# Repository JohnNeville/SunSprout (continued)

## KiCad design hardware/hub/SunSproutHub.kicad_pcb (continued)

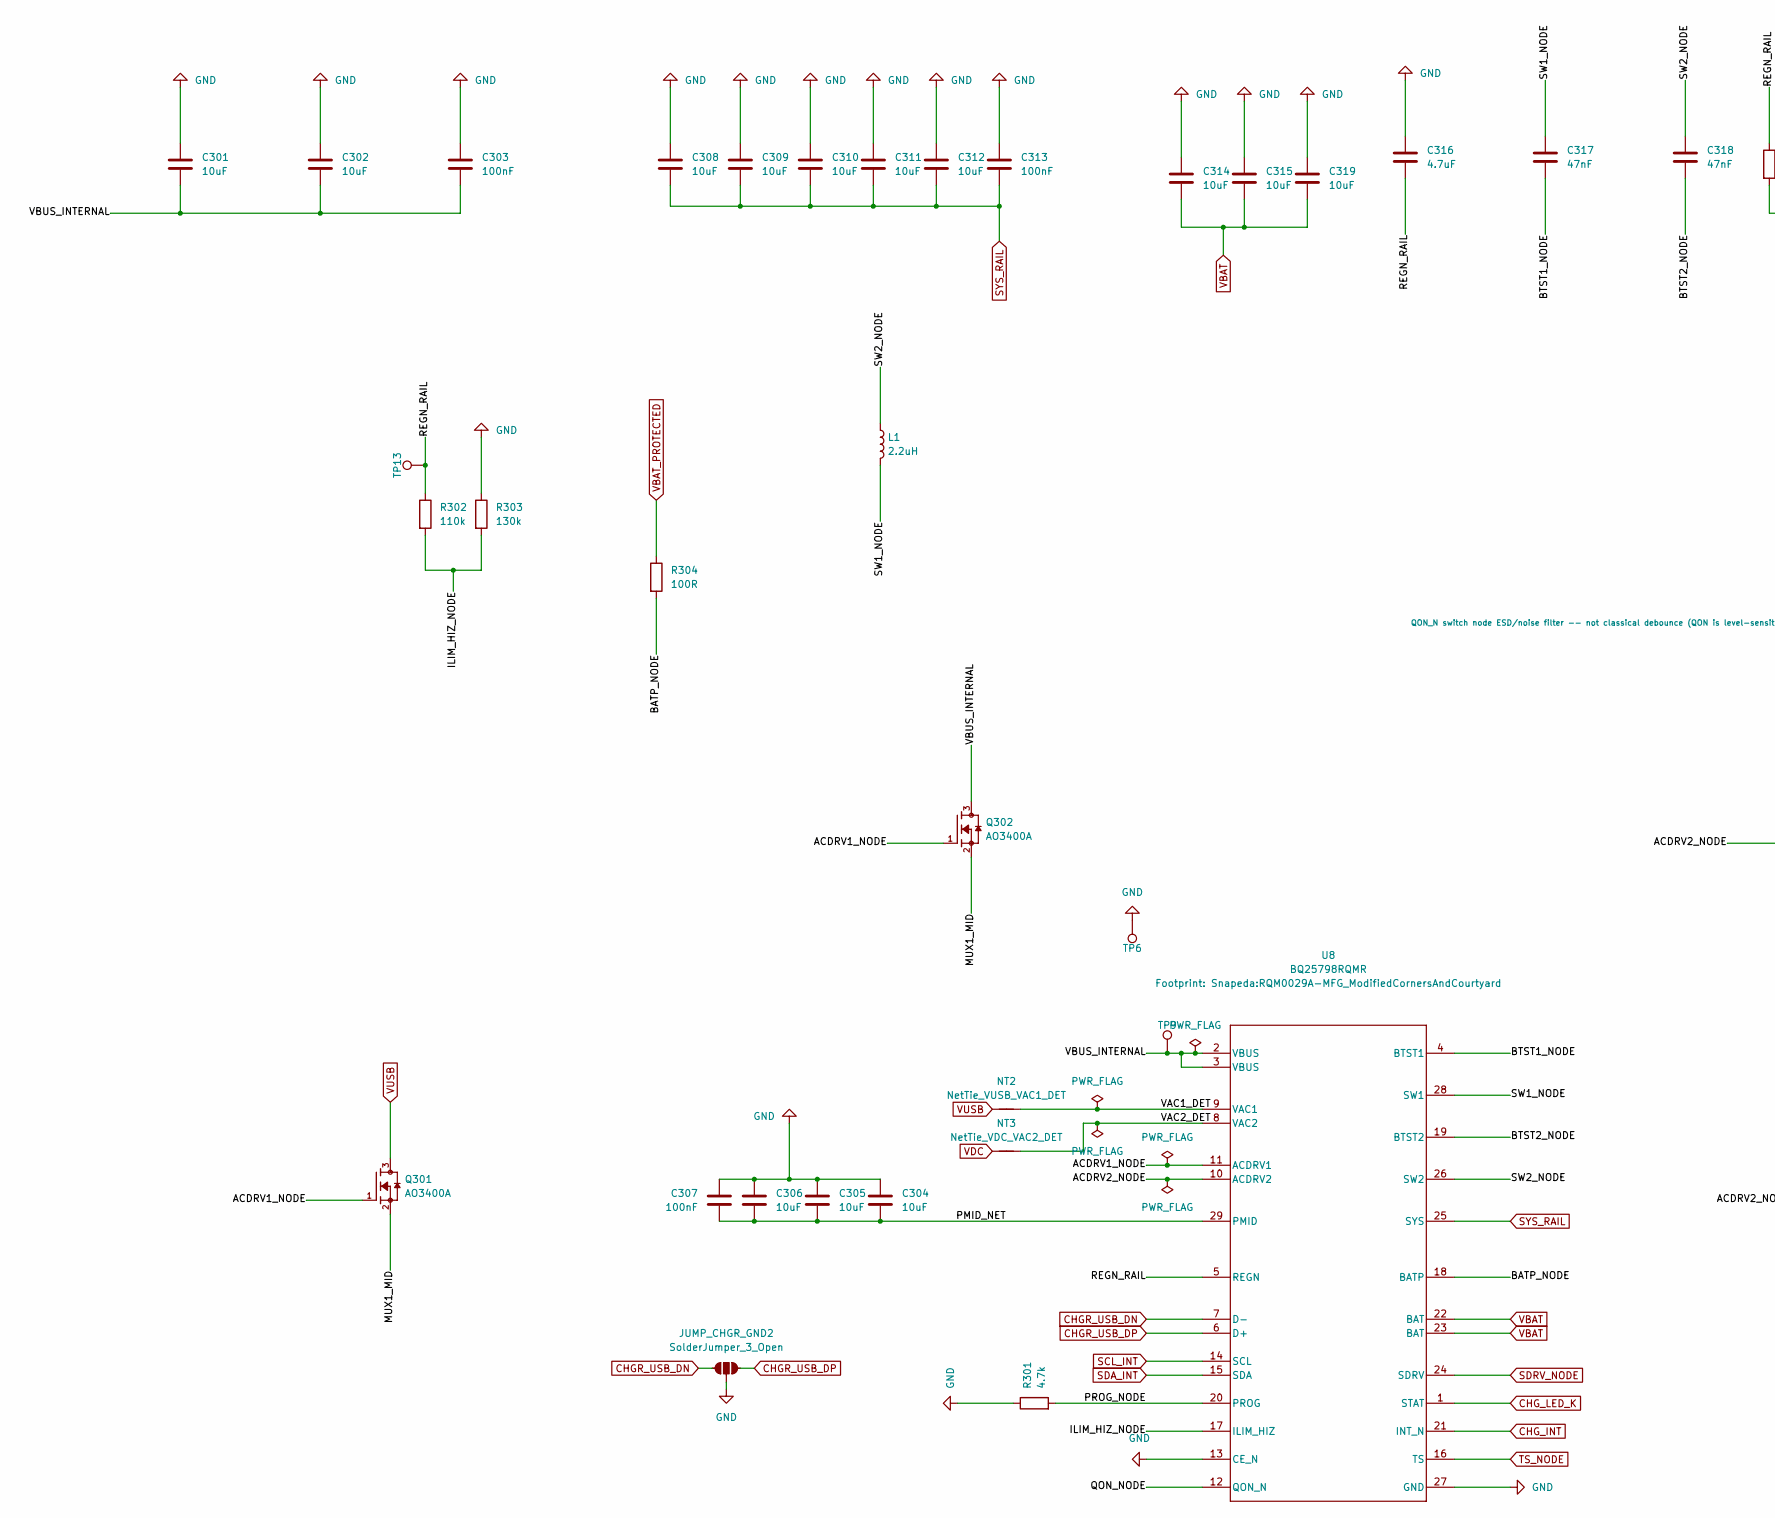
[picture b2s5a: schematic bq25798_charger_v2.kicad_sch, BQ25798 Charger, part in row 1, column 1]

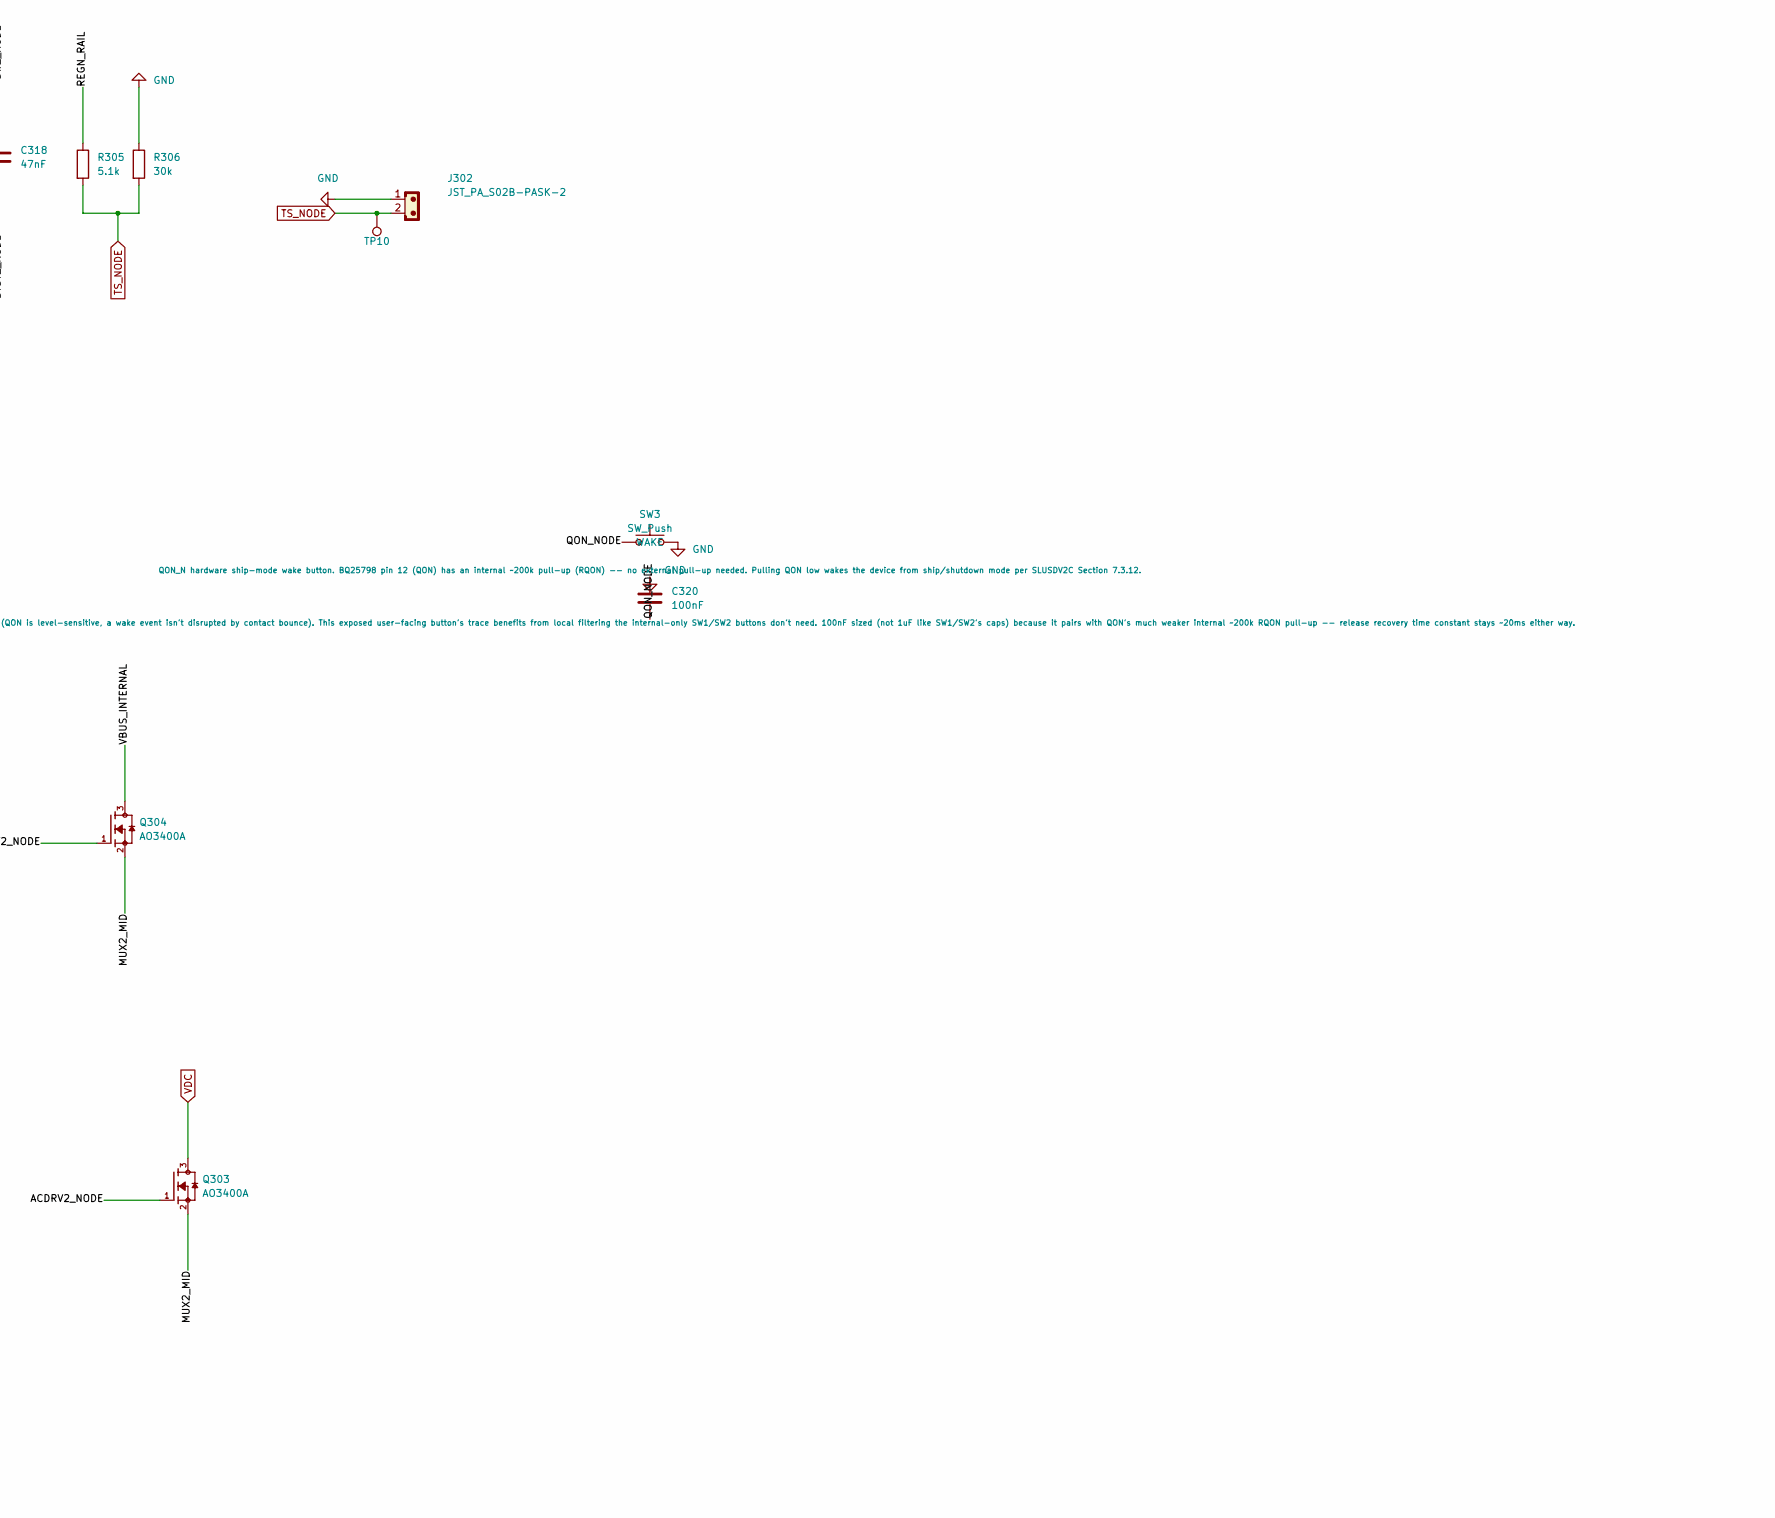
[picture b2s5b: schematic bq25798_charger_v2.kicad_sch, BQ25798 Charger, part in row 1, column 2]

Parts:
C301, C302, C304, C305, C306: 10uF; C_0805_2012Metric; MPN GRM21BR61H106KE43L; LCSC Part C440198
C303, C307, C313, C320: 100nF; C_0402; MPN CL05B104KB54PNC; LCSC Part C307331
C308, C309, C310, C311, C312, C314, C315, C319: 10uF; C_0603_1608Metric; MPN CL10A106MA8NRNC; LCSC Part C96446
C316: 4.7uF; C_0805_2012Metric; MPN CL21A475KAQNNNE; LCSC Part C1779
C317, C318: 47nF; C_0603_1608Metric; MPN CL10B473KB8NNNC; LCSC Part C1622
J302: JST_PA_S02B-PASK-2; JST_PA_S02B-PASK-2_1x02_P2.00mm_Horizontal; MPN S02B-PASK-2(LF)(SN); LCSC Part C265094
JUMP_CHGR_GND2: SolderJumper_3_Open; SolderJumper-3_P1.3mm_Open_RoundedPad1.0x1.5mm_NumberLabels
L1: 2.2uH; L_Changjiang_FTC404030S; MPN FTC404030S2R2MGCA; LCSC Part C39676081
NT2: NetTie_VUSB_VAC1_DET; NetTie-2_SMD_Pad0.5mm
NT3: NetTie_VDC_VAC2_DET; NetTie-2_SMD_Pad0.5mm
Q301, Q302, Q303, Q304: AO3400A; SOT95P280X125-3N; MPN AO3400A; LCSC Part C20917
R301: 4.7k; R_0603_1608Metric; MPN 0603WAF4701T5E; LCSC Part C23162
R302: 110k; R_0603_1608Metric; MPN 0603WAF1103T5E; LCSC Part C25805
R303: 130k; R_0603_1608Metric; MPN 0603WAF1303T5E; LCSC Part C22795
R304: 100R; R_0603_1608Metric; MPN 0603WAF1000T5E; LCSC Part C22775
R305: 5.1k; R_0603_1608Metric; MPN 0603WAF5101T5E; LCSC Part C23186
R306: 30k; R_0603_1608Metric; MPN 0603WAF3002T5E; LCSC Part C22984
SW3: SW_Push; SW_SPST_TS-1088-xR020; MPN TS-1088-AR02016; LCSC Part C720477
TP6: GND; TestPoint-1.0mm
TP9: VBUS_INTERNAL; TestPoint-1.0mm
TP10: TS_NODE; TestPoint-1.0mm
TP13: REGN_RAIL; TestPoint-1.0mm
U8: BQ25798RQMR; RQM0029A-MFG_ModifiedCornersAndCourtyard; MPN BQ25798RQMR; LCSC Part C2876593

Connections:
/BQ25798 Charger/ACDRV1_NODE: Q301.1, Q302.1, U8.11 (ACDRV1)
/BQ25798 Charger/ACDRV2_NODE: Q303.1, Q304.1, U8.10 (ACDRV2)
/BQ25798 Charger/BATP_NODE: R304.2, U8.18 (BATP)
/BQ25798 Charger/BTST1_NODE: C317.2, U8.4 (BTST1)
/BQ25798 Charger/BTST2_NODE: C318.2, U8.19 (BTST2)
/BQ25798 Charger/ILIM_HIZ_NODE: R302.2, R303.2, U8.17 (ILIM_HIZ)
/BQ25798 Charger/MUX1_MID: Q301.2, Q302.2
/BQ25798 Charger/MUX2_MID: Q303.2, Q304.2
/BQ25798 Charger/PMID_NET: C304.2, C305.2, C306.2, C307.2, U8.29 (PMID)
/BQ25798 Charger/PROG_NODE: R301.2, U8.20 (PROG)
/BQ25798 Charger/QON_NODE: C320.2, SW3.1, U8.12 (QON_N)
/BQ25798 Charger/REGN_RAIL: C316.2, R302.1, R305.1, TP13.1 (1_1), U8.5 (REGN)
/BQ25798 Charger/SW1_NODE: C317.1, L1.2, U8.28 (SW1)
/BQ25798 Charger/SW2_NODE: C318.1, L1.1, U8.26 (SW2)
/BQ25798 Charger/VAC1_DET: NT2.2, U8.9 (VAC1)
/BQ25798 Charger/VAC2_DET: NT3.2, U8.8 (VAC2)
/BQ25798 Charger/VBUS_INTERNAL: C301.2, C302.2, C303.2, Q302.3, Q304.3, TP9.1 (1_1), U8.2 (VBUS), U8.3 (VBUS)
CHGR_USB_DN: JUMP_CHGR_GND2.1 (A), U8.7 (D-); also elsewhere on the board
CHGR_USB_DP: JUMP_CHGR_GND2.3 (C), U8.6 (D+); also elsewhere on the board
CHG_INT: U8.21 (INT_N); also elsewhere on the board
CHG_LED_K: U8.1 (STAT); also elsewhere on the board
GND: C301.1, C302.1, C303.1, C304.1, C305.1, C306.1, C307.1, C308.1, C309.1, C310.1, C311.1, C312.1, C313.1, C314.1, C315.1, C316.1, C319.1, C320.1, J302.1, JUMP_CHGR_GND2.2 (B), R301.1, R303.1, R306.1, SW3.2, TP6.1 (1_1), U8.13 (CE_N), U8.27 (GND); also elsewhere on the board
SCL_INT: U8.14 (SCL); also elsewhere on the board
SDA_INT: U8.15 (SDA); also elsewhere on the board
SDRV_NODE: U8.24 (SDRV); also elsewhere on the board
SYS_RAIL: C308.2, C309.2, C310.2, C311.2, C312.2, C313.2, U8.25 (SYS); also elsewhere on the board
TS_NODE: J302.2, R305.2, R306.2, TP10.1 (1_1), U8.16 (TS)
VBAT: C314.2, C315.2, C319.2, U8.22 (BAT), U8.23 (BAT); also elsewhere on the board
VBAT_PROTECTED: R304.1; also elsewhere on the board
VDC: NT3.1, Q303.3; also elsewhere on the board
VUSB: NT2.1, Q301.3; also elsewhere on the board

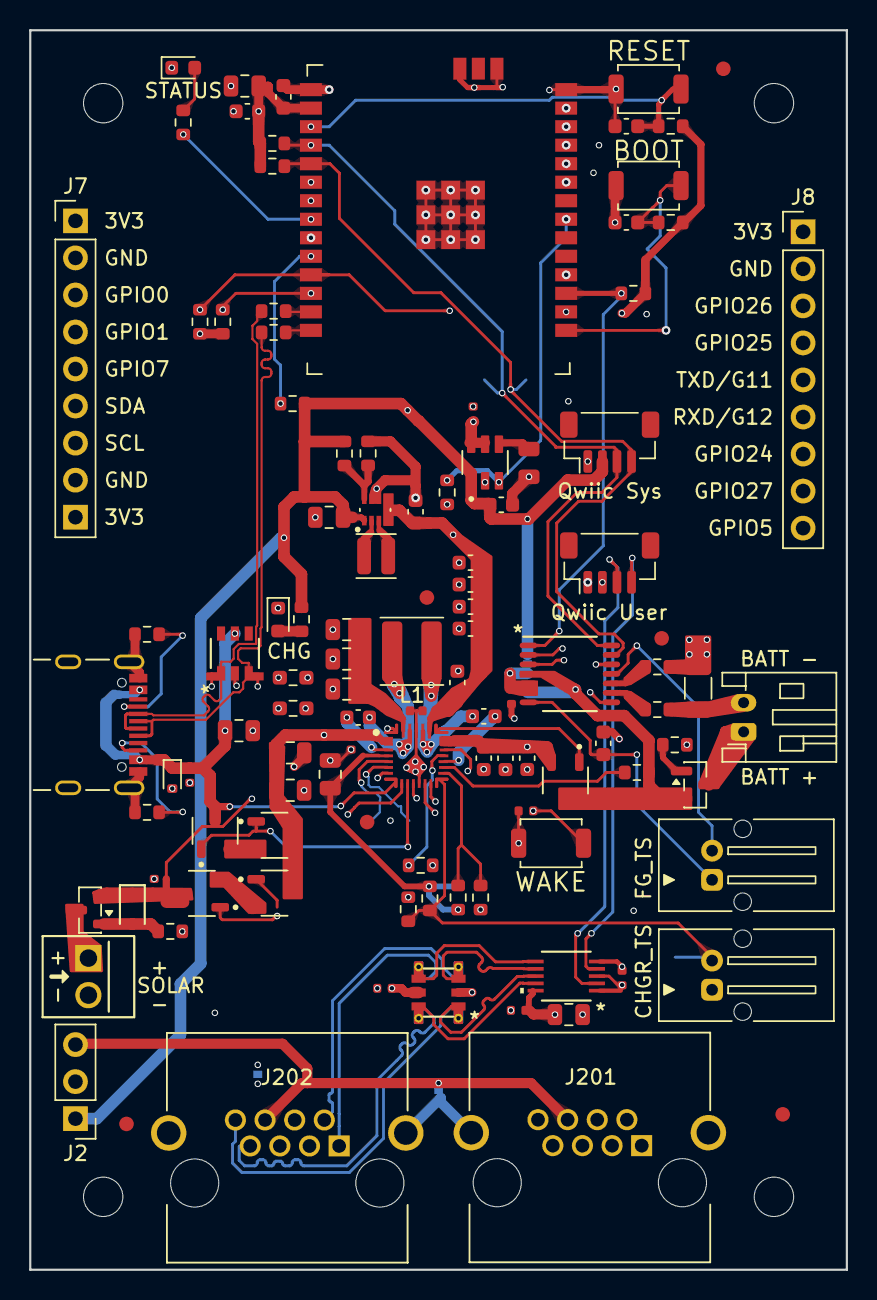
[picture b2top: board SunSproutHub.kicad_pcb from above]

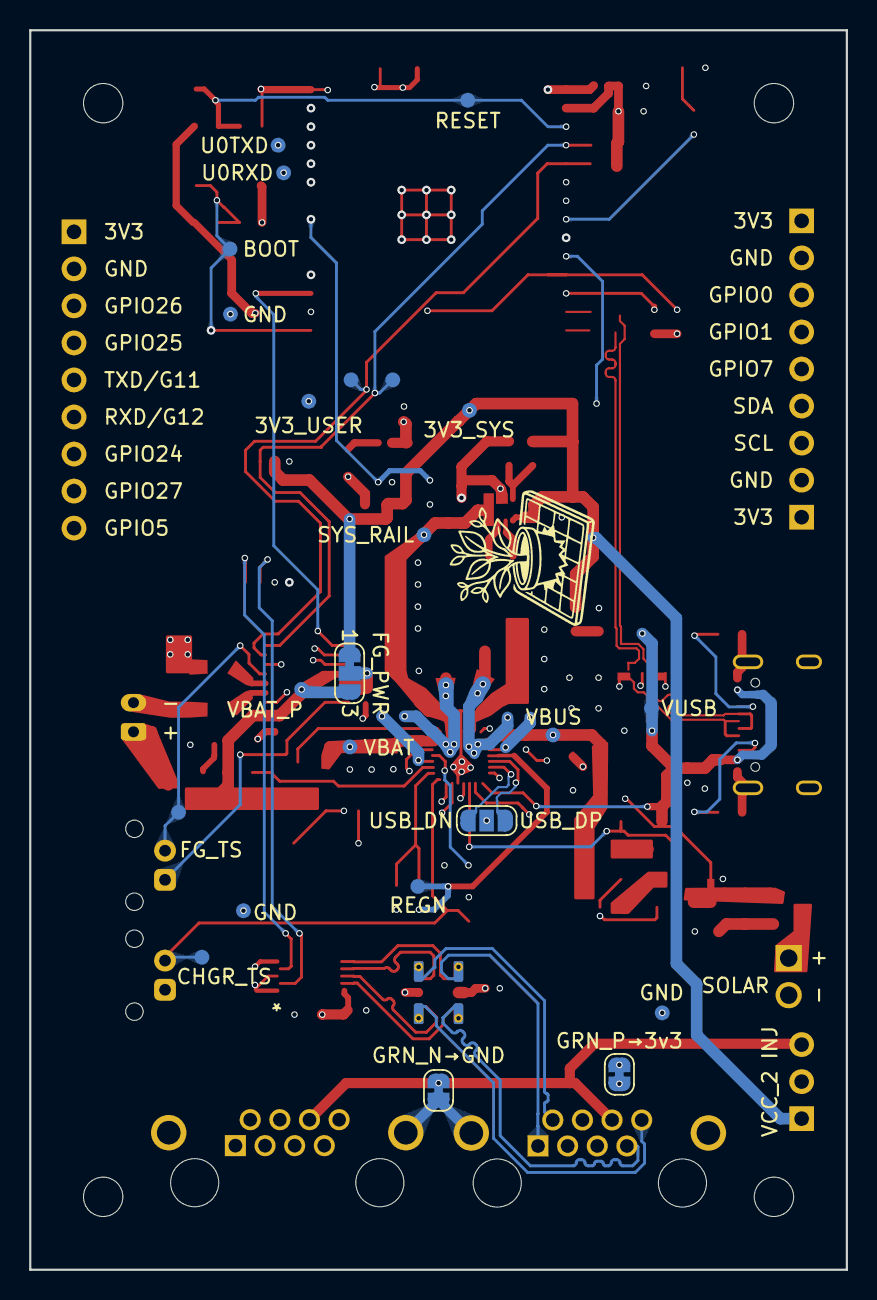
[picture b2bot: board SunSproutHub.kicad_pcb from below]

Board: 6 copper layers, 56.0 x 85.0 mm, 141 parts (23 on the bottom side), 90 nets.

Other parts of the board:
Fid1, Fid8, Fid9: Fiducial_1mm_Mask2mm
Fid6, Fid6#2, Fid7: (no value)
MH1, MH2, MH3, MH4: MountingHole_2.7mm_M2.5

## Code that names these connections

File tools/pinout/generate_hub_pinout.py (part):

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J7_PINS = [
    {"pin": 1, "board_y": 13.07, "tags": [("3V3_USER", "pwr"), ("Switched 3.3V", "pwr")]},
    {"pin": 2, "board_y": 15.61, "tags": [("GND", "gnd")]},
    {"pin": 3, "board_y": 18.15, "tags": [("GPIO0", "lp-gpio"), ("LP_GPIO0 / Wake", "lp-gpio")]},
    {"pin": 4, "board_y": 20.69, "tags": [("GPIO1", "gpio"), ("Free IO", "gpio")]},
    {"pin": 5, "board_y": 23.23, "tags": [("GPIO7", "gpio"), ("Free IO", "gpio"), ("SDIO Strap", "strap")]},
    {"pin": 6, "board_y": 25.77, "tags": [("GPIO9", "i2c-user"), ("SDA_USER", "i2c-user")]},
    {"pin": 7, "board_y": 28.31, "tags": [("GPIO10", "i2c-user"), ("SCL_USER", "i2c-user")]},
    {"pin": 8, "board_y": 30.85, "tags": [("GND", "gnd")]},
    {"pin": 9, "board_y": 33.39, "tags": [("3V3_USER", "pwr"), ("Switched 3.3V", "pwr")]},
]
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J8_PINS = [
    {"pin": 1, "board_y": 13.82, "tags": [("3V3_USER", "pwr"), ("Switched 3.3V", "pwr")]},
    {"pin": 2, "board_y": 16.36, "tags": [("GND", "gnd")]},
    {"pin": 3, "board_y": 18.90, "tags": [("GPIO26", "gpio"), ("Free IO", "gpio"), ("Boot Strap", "strap")]},
    {"pin": 4, "board_y": 21.44, "tags": [("GPIO25", "gpio"), ("Free IO", "gpio"), ("Boot Strap", "strap")]},
    {"pin": 5, "board_y": 23.98, "tags": [("GPIO11", "uart"), ("U0TXD (Console)", "uart")]},
    {"pin": 6, "board_y": 26.52, "tags": [("GPIO12", "uart"), ("U0RXD (Console)", "uart")]},
    {"pin": 7, "board_y": 29.06, "tags": [("GPIO24", "gpio"), ("Free IO", "gpio")]},
    {"pin": 8, "board_y": 31.60, "tags": [("GPIO27", "gpio"), ("Free IO", "gpio"), ("Boot Strap", "strap")]},
    {"pin": 9, "board_y": 34.14, "tags": [("GPIO5", "gpio"), ("Free IO", "gpio")]},
]

LEGEND_ITEMS = [
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        curr_x += (badge_w + 6)
    svg_lines.append('  </g>')

    # SW2 (Bootloader GPIO28)
    sw2_cx, sw2_cy = mm_to_canvas(42.40, 10.65)
    sw2_label_y = 118
    sw2_label_x = BOARD_X + BOARD_PIX_W + 120
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    svg_lines.append(f'    <path d="M {sw2_cx:.1f} {sw2_cy:.1f} L {sw2_cx + 40} {sw2_label_y} L {sw2_label_x} {sw2_label_y}" class="leader-line"/>')
    svg_lines.append(f'    <circle cx="{sw2_cx:.1f}" cy="{sw2_cy:.1f}" r="4.5" class="pin-dot pin-dot-strap"/>')
    curr_x = sw2_label_x + 6
    for text, tag_type in [("SW2", "btn"), ("GPIO28", "strap"), ("Download Boot Strap", "strap")]:
        badge_svg, badge_w = render_badge(curr_x, sw2_label_y, text, tag_type, is_right_aligned=False)
        svg_lines.append(f'    {badge_svg}')
        curr_x += (badge_w + 6)
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    svg_lines.append(f'    <path d="M {j203_cx:.1f} {j203_cy:.1f} L 870.0 {j203_cy:.1f} L 870.0 {j203_label_y} L {j203_label_x} {j203_label_y}" class="leader-line"/>')
    svg_lines.append(f'    <circle cx="{j203_cx:.1f}" cy="{j203_cy:.1f}" r="4.5" class="pin-dot pin-dot-i2c-user"/>')
    curr_x = j203_label_x + 6
    for text, tag_type in [("J203", "i2c-user"), ("STEMMA QT User", "i2c-user"), ("HP_I2C (GPIO9/10)", "i2c-user")]:
        badge_svg, badge_w = render_badge(curr_x, j203_label_y, text, tag_type, is_right_aligned=False)
        svg_lines.append(f'    {badge_svg}')
        curr_x += (badge_w + 6)
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    left_items = [
        ("TP17", 39.08, 7.96, "U0TXD Console TX", [("TP17", "uart"), ("U0TXD", "uart"), ("Console Transmit", "uart")], "uart", "uart"),
        ("TP16", 38.70, 9.85, "U0RXD Console RX", [("TP16", "uart"), ("U0RXD", "uart"), ("Console Receive", "uart")], "uart", "uart"),
        ("TP18", 42.38, 15.07, "BOOT Strap", [("TP18", "strap"), ("BOOT / GPIO28", "strap"), ("Download Boot Strap", "strap")], "strap,btn", "strap"),
        ("TP6", 42.34, 19.54, "Digital GND", [("TP6", "gnd"), ("GND", "gnd"), ("Digital Ground", "gnd")], "gnd", "gnd"),
        ("TP7", 36.97, 25.52, "3V3_USER Switched", [("TP7", "pwr"), ("3V3_USER", "pwr"), ("Switched 3.3V Rail", "pwr")], "pwr", "pwr"),
        ("TP15", 40.47, 45.28, "VBAT_PRO Protected", [("TP15", "pwr"), ("VBAT_PRO", "pwr"), ("Protected Battery", "pwr")], "pwr", "pwr"),
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
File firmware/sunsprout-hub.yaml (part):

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    # GPIO2 is the MTMS strapping pin, and the low-power I2C controller works on no other
    # pair, so the warning cannot be avoided; the board already carries this condition.
    sda:
      number: GPIO2   # SDA_INT / LP_I2C_SDA
      ignore_strapping_warning: true
    scl: GPIO3      # SCL_INT / LP_I2C_SCL
    low_power_mode: true
    scan: true

  # Switched user bus, behind the PCA9615 differential buffer. It has no power
  # until the 3V3_USER rail is enabled, so scanning it at boot finds nothing.
  - id: bus_user
    sda: GPIO9      # SDA_USER
    scl: GPIO10     # SCL_USER
    scan: false

# --- Charger ---------------------------------------------------------------
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    name: "Charger Interrupt"
    id: charger_interrupt
    pin:
      number: GPIO8      # CHG_INT
      inverted: true
    entity_category: diagnostic
    disabled_by_default: true
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    name: "Fuel Gauge Alert"
    id: fuel_gauge_alert
    pin:
      number: GPIO4      # FG_ALERT
      inverted: true
    entity_category: diagnostic
    disabled_by_default: true
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  - platform: gpio
    name: "User 3V3 Rail"
    id: user_rail
    pin: GPIO23          # EN_3V3_USER
    restore_mode: RESTORE_DEFAULT_OFF
    entity_category: config

output:
  - platform: gpio
    id: status_led_output
    pin: GPIO6           # LED1_CTRL, through R3

light:
  - platform: binary
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
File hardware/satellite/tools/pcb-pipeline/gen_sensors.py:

import sys
import os
sys.path.insert(0, os.path.dirname(os.path.abspath(__file__)))
import kicad_sch_builder as B

B.ROOT_UUID = "b8ad246c-0963-44e9-b36f-20d138e559cc"
SHEET_UUID = "5c3db235-7c84-4784-89d3-95a10e8212da"
DOC_UUID = "e5588b12-2498-4e97-87b3-4d3fcd02ed07"

LIB_IDS_USED = [
    "Analog_ADC:ADS1115IDGS", "Interface_Expansion:DS2484R",
    "Connector_Generic:Conn_01x03", "Jumper:SolderJumper_2_Bridged",
    "Jumper:SolderJumper_2_Open", "Device:C", "Device:R", "power:GND",
]

parts, wires, junctions, labels, pwr = [], [], [], [], []


def stub_label(pin_xy, net, dx=None, dy=None, shape="input"):
    x, y = pin_xy
    if dx is None and dy is None:
        dx = getattr(pin_xy, "dx", 10.16)
        dy = getattr(pin_xy, "dy", 0)
    elif dx is None:
        dx = 0
    elif dy is None:
        dy = 0
    dx = B.snap(dx)
    dy = B.snap(dy)
    ex, ey = B.snap(x + dx), B.snap(y + dy)
    wires.append(B.wire([(x, y), (ex, ey)]))
    if dx < 0:
        angle, justify = 180, "right"
    elif dx > 0:
        angle, justify = 0, "left"
    elif dy < 0:
        angle, justify = 90, "left"
    else:  # dy > 0
        angle, justify = 270, "right"
    labels.append(B.global_label(net, shape, ex, ey, angle, justify))


# ---------------------------------------------------------------------------
# J2-J5: moisture sensor connectors (JST PH 3-pin)
# Placed on left at x=38.1 with generous 25.4mm vertical spacing
j2_block, J2 = B.symbol_instance(
    "Connector_Generic:Conn_01x03", "J2", "Conn_01x03", 38.1, 25.4, 0, SHEET_UUID,
    footprint="Connector_JST:JST_PH_B3B-PH-K_1x03_P2.00mm_Vertical",
    usage="DFRobot Gravity PH2.0-3P connector for analog capacitive soil moisture sensor 1 (Channel A0)",
    lcsc="C131339", ft_pos="", ft_rot=""
)
j3_block, J3 = B.symbol_instance(
    "Connector_Generic:Conn_01x03", "J3", "Conn_01x03", 38.1, 50.8, 0, SHEET_UUID,
    footprint="Connector_JST:JST_PH_B3B-PH-K_1x03_P2.00mm_Vertical",
    usage="DFRobot Gravity PH2.0-3P connector for analog capacitive soil moisture sensor 2 (Channel A1)",
    lcsc="C131339", ft_pos="", ft_rot=""
)
j4_block, J4 = B.symbol_instance(
    "Connector_Generic:Conn_01x03", "J4", "Conn_01x03", 38.1, 76.2, 0, SHEET_UUID,
    footprint="Connector_JST:JST_PH_B3B-PH-K_1x03_P2.00mm_Vertical",
    usage="DFRobot Gravity PH2.0-3P connector for analog capacitive soil moisture sensor 3 (Channel A2)",
    lcsc="C131339", ft_pos="", ft_rot=""
)
j5_block, J5 = B.symbol_instance(
    "Connector_Generic:Conn_01x03", "J5", "Conn_01x03", 38.1, 101.6, 0, SHEET_UUID,
    footprint="Connector_JST:JST_PH_B3B-PH-K_1x03_P2.00mm_Vertical",
    usage="DFRobot Gravity PH2.0-3P connector for analog capacitive soil moisture sensor 4 (Channel A3)",
    lcsc="C131339", ft_pos="", ft_rot=""
)
parts += [j2_block, j3_block, j4_block, j5_block]

# JP1-4: ADS1115 address-select solder jumpers (spaced generously along top at y=25.4, 50.8mm apart to avoid stub collisions)
jp1_block, JP1 = B.symbol_instance(
    "Jumper:SolderJumper_2_Bridged", "JP1", "SolderJumper_2_Bridged", 76.2, 25.4, 0, SHEET_UUID,
    footprint="Jumper:SolderJumper-2_P1.3mm_Bridged_RoundedPad1.0x1.5mm",
    usage="Solder jumper tying ADS1115 ADDR pin to GND (sets I2C address 0x48, default closed)",
    lcsc="", ft_pos="", ft_rot=""
)
jp2_block, JP2 = B.symbol_instance(
    "Jumper:SolderJumper_2_Open", "JP2", "SolderJumper_2_Open", 127.0, 25.4, 0, SHEET_UUID,
    footprint="Jumper:SolderJumper-2_P1.3mm_Open_RoundedPad1.0x1.5mm",
    usage="Solder jumper tying ADS1115 ADDR pin to SAT_3V3 (sets I2C address 0x49)",
    lcsc="", ft_pos="", ft_rot=""
)
jp3_block, JP3 = B.symbol_instance(
    "Jumper:SolderJumper_2_Open", "JP3", "SolderJumper_2_Open", 177.8, 25.4, 0, SHEET_UUID,
    footprint="Jumper:SolderJumper-2_P1.3mm_Open_RoundedPad1.0x1.5mm",
    usage="Solder jumper tying ADS1115 ADDR pin to SDA_LOCAL (sets I2C address 0x4A)",
    lcsc="", ft_pos="", ft_rot=""
)
jp4_block, JP4 = B.symbol_instance(
    "Jumper:SolderJumper_2_Open", "JP4", "SolderJumper_2_Open", 228.6, 25.4, 0, SHEET_UUID,
    footprint="Jumper:SolderJumper-2_P1.3mm_Open_RoundedPad1.0x1.5mm",
    usage="Solder jumper tying ADS1115 ADDR pin to SCL_LOCAL (sets I2C address 0x4B)",
    lcsc="", ft_pos="", ft_rot=""
)
parts += [jp1_block, jp2_block, jp3_block, jp4_block]

# U2: ADS1115 ADC (placed at x=88.9, y=88.9)
u2_block, U2 = B.symbol_instance(
    "Analog_ADC:ADS1115IDGS", "U2", "ADS1115IDGS", 88.9, 88.9, 0, SHEET_UUID,
    footprint="Package_SO:TSSOP-10_3x3mm_P0.5mm",
    usage="16-bit 4-channel precision delta-sigma ADC measuring analog soil moisture sensor voltages over I2C",
    lcsc="C37593", ft_pos="", ft_rot=""
)
parts.append(u2_block)

# U3: DS2484R 1-Wire bridge (placed at x=165.1, y=88.9, spaced 76.2mm from U2)
u3_block, U3 = B.symbol_instance(
    "Interface_Expansion:DS2484R", "U3", "DS2484R", 165.1, 88.9, 0, SHEET_UUID,
    footprint="Package_TO_SOT_SMD:SOT-23-6",
    usage="I2C to 1-Wire bridge with internal pull-up and slew rate control interfacing external DS18B20 temperature sensors",
    lcsc="C124886", ft_pos="", ft_rot=""
)
parts.append(u3_block)

# J6: 1-Wire temp probe connector (placed on far right at x=241.3, y=88.9)
j6_block, J6 = B.symbol_instance(
    "Connector_Generic:Conn_01x03", "J6", "Conn_01x03", 241.3, 88.9, 0, SHEET_UUID,
    footprint="Connector_JST:JST_PH_B3B-PH-K_1x03_P2.00mm_Vertical",
    usage="JST PA 3-pin connector for daisy-chained external DS18B20 1-Wire waterproof temperature probes",
    lcsc="C131339", ft_pos="", ft_rot=""
)
parts.append(j6_block)

# Decoupling caps (placed cleanly below ICs at y=152.4)
c4_block, C4 = B.symbol_instance(
    "Device:C", "C4", "100nF", 88.9, 152.4, 0, SHEET_UUID,
    footprint="Capacitor_SMD:C_0603_1608Metric",
    usage="High-frequency local bypass decoupling for ADS1115 VDD supply rail",
    lcsc="C14663", ft_pos="", ft_rot=""
)
c5_block, C5 = B.symbol_instance(
    "Device:C", "C5", "100nF", 165.1, 152.4, 0, SHEET_UUID,
    footprint="Capacitor_SMD:C_0603_1608Metric",
    usage="High-frequency local bypass decoupling for DS2484R VDD/VCC supply rails",
    lcsc="C14663", ft_pos="", ft_rot=""
)

# R9: Optional 1-Wire passive pull-up resistor (DNP by default; solder 4.7k 0603 if needed)
r9_block, R9 = B.symbol_instance(
    "Device:R", "R9", "4.7k", 203.2, 152.4, 0, SHEET_UUID,
    footprint="Resistor_SMD:R_0603_1608Metric",
    usage="Optional 1-Wire passive pull-up resistor to SAT_3V3 (DNP by default; populate 4.7k 0603 if external passive pull-up is needed for long cable runs)",
    lcsc="C23162", ft_pos="", ft_rot="", dnp=True
)
parts += [c4_block, c5_block, r9_block]

# ---------------------------------------------------------------------------
# Wiring - net-connections.md, "Sheet 2 - Sensors"

for pin_xy in [U2["8"], U3["6"], U3["1"], C4["1"], C5["1"], R9["1"], J2["2"], J3["2"], J4["2"], J5["2"], J6["1"], JP2["2"]]:
    stub_label(pin_xy, "SAT_3V3")

for pin_xy in [U2["3"], U3["4"], C4["2"], C5["2"], J2["1"], J3["1"], J4["1"], J5["1"], J6["2"], JP1["2"]]:
    stub_label(pin_xy, "GND")

for pin_xy in [U2["9"], U3["2"], JP3["2"]]:
    stub_label(pin_xy, "SDA_LOCAL")
for pin_xy in [U2["10"], U3["3"], JP4["2"]]:
    stub_label(pin_xy, "SCL_LOCAL")

for pin_xy in [U2["1"], JP1["1"], JP2["1"], JP3["1"], JP4["1"]]:
    stub_label(pin_xy, "ADDR_SEL")

stub_label(U3["5"], "ONEWIRE_DQ")
stub_label(J6["3"], "ONEWIRE_DQ")
stub_label(R9["2"], "ONEWIRE_DQ")

stub_label(U2["4"], "MOIST1")
stub_label(J2["3"], "MOIST1")
stub_label(U2["5"], "MOIST2")
stub_label(J3["3"], "MOIST2")
stub_label(U2["6"], "MOIST3")
stub_label(J4["3"], "MOIST3")
stub_label(U2["7"], "MOIST4")
stub_label(J5["3"], "MOIST4")

# U2.ALERT (pin2) intentionally left NC per design
ncs = [B.no_connect(*U2["2"])]

lib_symbols_block = B.build_lib_symbols_block(LIB_IDS_USED)
out = [B.sheet_header("Sensors", DOC_UUID, lib_symbols_block)]
out += parts + wires + junctions + labels + pwr + ncs
out.append(B.sheet_footer())

sch_text = "\n".join(out)
out_file = os.path.join(os.path.dirname(os.path.abspath(__file__)), "sensors.kicad_sch")
with open(out_file, "w", encoding="utf-8") as f:
    f.write(sch_text)
print(f"wrote {out_file}")

sheet_file = os.path.join(B.PROJECT_ROOT, "sheets", "sensors_v1.kicad_sch")
if os.path.exists(os.path.dirname(sheet_file)):
    with open(sheet_file, "w", encoding="utf-8") as f:
        f.write(sch_text)
    print(f"wrote {sheet_file}")

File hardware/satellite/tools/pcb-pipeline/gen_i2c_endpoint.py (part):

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- Zone 3 (Center-Right): U4 (USBLC6-4SC6) ESD protection + local bypass C6 directly adjacent.
- Zone 4 (Right): J1 (RJ45 jack) + Power Distribution & Grounding Block:
  C1 (22uF bulk cap) + JP14 (power source select) + JP15 (GND_2 bridge) +
  JP13 (shield GND) + J7 (aux 2.54mm pin header).
"""
import sys
import os
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u4_block, U4 = B.symbol_instance(
    "Power_Protection:USBLC6-4SC6", "U4", "USBLC6-4SC6", 139.7, 114.3, 0, SHEET_UUID,
    footprint="Package_TO_SOT_SMD:SOT-23-6",
    usage="Low-capacitance ESD protection diode array clamping the 4 differential I2C lines to SAT_3V3 and GND at the RJ45 cable entry",
    lcsc="C5180279", ft_pos="", ft_rot=""
)
parts.append(u4_block)
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
# SAT_3V3
for pin_xy in [U1["1"], U1["3"], U1["10"], U4["5"], C1["1"], C2["1"], C3["1"], C6["1"], JP14["2"]]:
    stub_label(pin_xy, "SAT_3V3")

# JP11 wiring to R1, R2
direct_wire(JP11["2"], R1["1"])
direct_wire(JP11["3"], R2["1"])
stub_label(JP11["1"], "SAT_3V3")

# GND
for pin_xy in [U1["5"], U4["2"], C1["2"], C2["2"], C3["2"], C6["2"], R5["2"], R8["2"], J1["5"], JP13["2"], JP15["2"]]:
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    stub_label(pin_xy, "GND_2")

# SHIELD
stub_label(J1["SH1"], "SHIELD")
stub_label(J1["SH2"], "SHIELD")
stub_label(JP13["1"], "SHIELD")

# SDA_LOCAL / SCL_LOCAL (shared bus - continues onto Sheets 2 & 3)
stub_label(U1["2"], "SDA_LOCAL")
stub_label(R2["2"], "SDA_LOCAL")
stub_label(U1["4"], "SCL_LOCAL")
stub_label(R1["2"], "SCL_LOCAL")

# DSCL_N / DSCL_P
for pin_xy in [J1["1"], U1["6"], U4["3"]]:
    stub_label(pin_xy, "DSCL_N")
for pin_xy in [J1["2"], U1["7"], U4["1"]]:
    stub_label(pin_xy, "DSCL_P")

# DSCL Termination Ladder: SAT_3V3 -> R3 -> DSCL_P -> R4 -> DSCL_N -> R5 -> GND
stub_label(R3["1"], "SAT_3V3")

# Node DSCL_P between R3 and R4
mid_dscl_p = (127.0, 38.1)
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wires.append(B.wire([mid_dscl_p, R4["1"]]))
wires.append(B.wire([mid_dscl_p, (137.16, 38.1)]))
junctions.append(B.junction(*mid_dscl_p))
labels.append(B.global_label("DSCL_P", "input", 137.16, 38.1, 0, "left"))

# Node DSCL_N between R4 and R5
mid_dscl_n = (127.0, 63.5)
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wires.append(B.wire([mid_dscl_n, R5["1"]]))
wires.append(B.wire([mid_dscl_n, (137.16, 63.5)]))
junctions.append(B.junction(*mid_dscl_n))
labels.append(B.global_label("DSCL_N", "input", 137.16, 63.5, 0, "left"))

# R5 pin 2 connects to GND (already included in GND list above)

# DSDA_N / DSDA_P
for pin_xy in [J1["7"], U1["9"], U4["6"]]:
    stub_label(pin_xy, "DSDA_N")
for pin_xy in [J1["8"], U1["8"], U4["4"]]:
    stub_label(pin_xy, "DSDA_P")

# DSDA Termination Ladder: SAT_3V3 -> R6 -> DSDA_P -> R7 -> DSDA_N -> R8 -> GND
stub_label(R6["1"], "SAT_3V3")

# Node DSDA_P between R6 and R7
mid_dsda_p = (177.8, 38.1)
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wires.append(B.wire([mid_dsda_p, R7["1"]]))
wires.append(B.wire([mid_dsda_p, (187.96, 38.1)]))
junctions.append(B.junction(*mid_dsda_p))
labels.append(B.global_label("DSDA_P", "input", 187.96, 38.1, 0, "left"))

# Node DSDA_N between R7 and R8
mid_dsda_n = (177.8, 63.5)
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wires.append(B.wire([mid_dsda_n, R8["1"]]))
wires.append(B.wire([mid_dsda_n, (187.96, 63.5)]))
junctions.append(B.junction(*mid_dsda_n))
labels.append(B.global_label("DSDA_N", "input", 187.96, 63.5, 0, "left"))

# R8 pin 2 connects to GND (already included in GND list above)

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
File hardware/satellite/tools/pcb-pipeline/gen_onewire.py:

"""Generate Sheet 3: 1-Wire Temperature Interface (onewire_v1.kicad_sch)
I2C to 1-Wire master bridge (DS2482S-100+) with configurable address (0x18-0x1B)
and external DS18B20 connector.
Layout:
- Address jumpers JP16 & JP17 grouped together in an address configuration block on left.
- U3 (DS2482S-100+) placed centrally, with local decoupling C5 and pull-up R9 grouped directly with U3.
- J6 probe connector placed on the right.
"""
import sys
import os
sys.path.insert(0, os.path.dirname(os.path.abspath(__file__)))
import kicad_sch_builder as B

B.ROOT_UUID = "b8ad246c-0963-44e9-b36f-20d138e559cc"
SHEET_UUID = "7d42e811-9a1b-4f5c-89b2-3e2c918a5411"
DOC_UUID = "f6699c23-35a9-4b08-98c4-5e4fde13fe18"

LIB_IDS_USED = [
    "project:DS2482S-100",
    "Connector_Generic:Conn_01x03",
    "Jumper:SolderJumper_3_Bridged12",
    "Device:C",
    "Device:R",
    "power:GND",
]

parts, wires, junctions, labels, pwr = [], [], [], [], []


def stub_label(pin_xy, net, dx=None, dy=None, shape="input"):
    x, y = pin_xy
    if dx is None and dy is None:
        dx = getattr(pin_xy, "dx", 10.16)
        dy = getattr(pin_xy, "dy", 0)
    elif dx is None:
        dx = 0
    elif dy is None:
        dy = 0
    dx = B.snap(dx)
    dy = B.snap(dy)
    ex, ey = B.snap(x + dx), B.snap(y + dy)
    wires.append(B.wire([(x, y), (ex, ey)]))
    if dx < 0:
        angle, justify = 180, "right"
    elif dx > 0:
        angle, justify = 0, "left"
    elif dy < 0:
        angle, justify = 90, "left"
    else:  # dy > 0
        angle, justify = 270, "right"
    labels.append(B.global_label(net, shape, ex, ey, angle, justify))


# ---------------------------------------------------------------------------
# Address Selection Jumper Group (grouped together at x=50.8)
# JP16 (AD0) and JP17 (AD1): 3-pad jumpers (Pin 1=GND, Pin 2=ADx, Pin 3=SAT_3V3; default 1-2 bridged -> 0x18)
jp16_block, JP16 = B.symbol_instance(
    "Jumper:SolderJumper_3_Bridged12", "JP16", "SolderJumper_3_Bridged12", 50.8, 63.5, 0, SHEET_UUID,
    footprint="Jumper:SolderJumper-3_P1.3mm_Bridged12_RoundedPad1.0x1.5mm",
    usage="Solder jumper for DS2482S-100 AD0 address bit (1-2 bridged to GND for 0, cut & bridge 2-3 to SAT_3V3 for 1; default 0)",
    lcsc="", ft_pos="", ft_rot="", hide_value=True
)
jp17_block, JP17 = B.symbol_instance(
    "Jumper:SolderJumper_3_Bridged12", "JP17", "SolderJumper_3_Bridged12", 50.8, 95.25, 0, SHEET_UUID,
    footprint="Jumper:SolderJumper-3_P1.3mm_Bridged12_RoundedPad1.0x1.5mm",
    usage="Solder jumper for DS2482S-100 AD1 address bit (1-2 bridged to GND for 0, cut & bridge 2-3 to SAT_3V3 for 1; default 0)",
    lcsc="", ft_pos="", ft_rot="", hide_value=True
)
parts += [jp16_block, jp17_block]

# ---------------------------------------------------------------------------
# U3: DS2482S-100+ 1-Wire Bridge & Local Passives Group (placed centrally at x=127.0)
u3_block, U3 = B.symbol_instance(
    "project:DS2482S-100", "U3", "DS2482S-100+", 127.0, 76.2, 0, SHEET_UUID,
    footprint="Package_SO:SOIC-8_3.9x4.9mm_P1.27mm",
    usage="I2C to 1-Wire bridge with active pull-up and 4 selectable I2C addresses (0x18-0x1B) interfacing external DS18B20 temperature probes",
    lcsc="C143306", ft_pos="", ft_rot=""
)
parts.append(u3_block)

# C5: Decoupling capacitor grouped directly below U3
c5_block, C5 = B.symbol_instance(
    "Device:C", "C5", "100nF", 127.0, 120.65, 0, SHEET_UUID,
    footprint="Capacitor_SMD:C_0603_1608Metric",
    usage="High-frequency local bypass decoupling for DS2482S-100 VCC supply rail",
    lcsc="C14663", ft_pos="", ft_rot=""
)
parts.append(c5_block)

# R9: Optional 1-Wire passive pull-up resistor grouped adjacent to U3/J6
r9_block, R9 = B.symbol_instance(
    "Device:R", "R9", "4.7k", 165.1, 120.65, 0, SHEET_UUID,
    footprint="Resistor_SMD:R_0603_1608Metric",
    usage="Optional 1-Wire passive pull-up resistor to SAT_3V3 (DNP by default; populate 4.7k 0603 if external passive pull-up is needed for long cable runs)",
    lcsc="C23162", ft_pos="", ft_rot="", dnp=True
)
parts.append(r9_block)

# ---------------------------------------------------------------------------
# J6: 1-Wire Temp Probe Connector (JST PA 3-pin)
j6_block, J6 = B.symbol_instance(
    "Connector_Generic:Conn_01x03", "J6", "Conn_01x03", 203.2, 76.2, 0, SHEET_UUID,
    footprint="Connector_JST:JST_PH_B3B-PH-K_1x03_P2.00mm_Vertical",
    usage="JST PA 3-pin connector for daisy-chained external DS18B20 1-Wire waterproof temperature probes",
    lcsc="C131339", ft_pos="", ft_rot=""
)
parts.append(j6_block)

# ---------------------------------------------------------------------------
# Wiring
# Power connections
for pin_xy in [U3["1"], C5["1"], R9["1"], J6["1"], JP16["3"], JP17["3"]]:
    stub_label(pin_xy, "SAT_3V3")

for pin_xy in [U3["3"], C5["2"], J6["2"], JP16["1"], JP17["1"]]:
    stub_label(pin_xy, "GND")

# I2C connections
stub_label(U3["5"], "SDA_LOCAL")
stub_label(U3["4"], "SCL_LOCAL")

# Address selection connections
stub_label(U3["7"], "AD0_SEL")
stub_label(JP16["2"], "AD0_SEL")

stub_label(U3["8"], "AD1_SEL")
stub_label(JP17["2"], "AD1_SEL")

# 1-Wire bus
stub_label(U3["2"], "ONEWIRE_DQ")
stub_label(J6["3"], "ONEWIRE_DQ")
stub_label(R9["2"], "ONEWIRE_DQ")

# U3.PCTLZ (pin 6) active-low strong pull-up control is not used with internal pull-up
ncs = [B.no_connect(*U3["6"])]

lib_symbols_block = B.build_lib_symbols_block(LIB_IDS_USED)
out = [B.sheet_header("1-Wire Temperature Interface", DOC_UUID, lib_symbols_block)]
out += parts + wires + junctions + labels + pwr + ncs
out.append(B.sheet_footer())

sch_text = "\n".join(out)
out_file = os.path.join(os.path.dirname(os.path.abspath(__file__)), "onewire.kicad_sch")
with open(out_file, "w", encoding="utf-8") as f:
    f.write(sch_text)
print(f"wrote {out_file}")

sheet_file = os.path.join(B.PROJECT_ROOT, "sheets", "onewire_v1.kicad_sch")
if os.path.exists(os.path.dirname(sheet_file)):
    with open(sheet_file, "w", encoding="utf-8") as f:
        f.write(sch_text)
    print(f"wrote {sheet_file}")
